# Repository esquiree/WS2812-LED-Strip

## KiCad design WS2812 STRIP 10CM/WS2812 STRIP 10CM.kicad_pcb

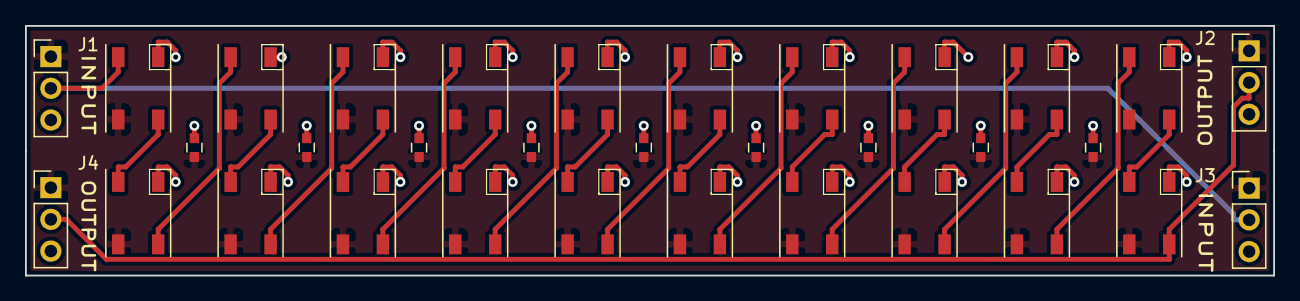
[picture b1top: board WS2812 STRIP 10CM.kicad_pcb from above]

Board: 2 copper layers, 100.0 x 20.0 mm, 33 parts (0 on the bottom side), 23 nets.

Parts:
C1, C2, C3, C4, C5, C6, C7, C8, C9: 100nF; C_0603
J1, J2, J3, J4: Conn_01x03; Pin_Header_Straight_1x03_Pitch2.54mm
U1, U2, U3, U4, U5, U6, U7, U8, U9, U10, U11, U12, U13, U14, U15, U16, U17, U18, U19, U20: WS2812B; WS2812B_Ver2

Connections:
GND: C1.2, C2.2, C3.2, C4.2, C5.2, C6.2, C7.2, C8.2, C9.2, J1.3, J2.3, J3.3, J4.3, U1.3, U2.3, U3.3, U4.3, U5.3, U6.3, U7.3, U8.3, U9.3, U10.3, U11.3, U12.3, U13.3, U14.3, U15.3, U16.3, U17.3, U18.3, U19.3, U20.3
unnamed: U1.2, U2.4
unnamed: U2.2, U3.4
unnamed: U3.2, U4.4
unnamed: U4.2, U5.4
unnamed: U5.2, U6.4
unnamed: U6.2, U7.4
unnamed: U7.2, U8.4
unnamed: U8.2, U9.4
unnamed: U10.2, U11.4
unnamed: U9.2, U10.4
unnamed: U11.2, U12.4
unnamed: U12.2, U13.4
unnamed: U13.2, U14.4
unnamed: U14.2, U15.4
unnamed: U15.2, U16.4
unnamed: U16.2, U17.4
unnamed: U17.2, U18.4
unnamed: U18.2, U19.4
unnamed: U19.2, U20.4
SIG_IN: J1.2, J3.2, U1.4
SIG_OUT: J2.2, J4.2, U20.2
VCC: C1.1, C2.1, C3.1, C4.1, C5.1, C6.1, C7.1, C8.1, C9.1, J1.1, J2.1, J3.1, J4.1, U1.1, U2.1, U3.1, U4.1, U5.1, U6.1, U7.1, U8.1, U9.1, U10.1, U11.1, U12.1, U13.1, U14.1, U15.1, U16.1, U17.1, U18.1, U19.1, U20.1

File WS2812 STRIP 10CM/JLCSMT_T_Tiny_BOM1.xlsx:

Comment | References | Footprint
0.1uF | C3 C4 C5 C6 C7 C8 C9 | 0603_C
WS2812B-B | U1 U2 U3 U4 U5 U6 U7 U8 U9 U10 U11 U12 U13 U14 U15 U16 U17 U18 U19 U20 | WS2812B
